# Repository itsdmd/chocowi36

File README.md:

# chocowi36

> A 36-key, low profile, wireless, split keyboard. Derived from [davidphilipbarr/Choc-Spaced-Corne](https://github.com/davidphilipbarr/Choc-Spaced-Corne), with the original design based on [Foostan's Corne](https://github.com/foostan/crkbd).

## Changes

-   The PCB shape, dimensions and mounting holes' position are modified to personal preferences.
-   Battery onboard connector is replaced with through hole pads for better flexibility. Power switch is connected to the positive terminal of the battery instead of ground.
-   The outermost thumb key has been changed to a 1u key, and the splayed angle of the thumb cluster has been increased to 15 degrees.
-   Allow the nice!nano to be mounted with the USB port facing down for both halves for better MCB protection.
-   Support both hotswap and soldered switches. Only Choc v1 switches are supported.

## Case

The case for the keyboard can be found here: [OnShape document](https://cad.onshape.com/documents/46b39ce86a53def7590272f1/w/488db377576b09efc6e15f6f/e/8a81a5fcc0753b2088ec2435)

This case features a 5.5x2.1 DC power jack for connecting to a detachable Li-Ion battery enclosure. The provided enclosure is designed for storing a 21700 battery with a protection PCB attached to it. This enclosure can act as a tenting mechanism, or for locking the two keyboard halves in place when folded for travelling. Most parameters can be _slightly_ adjust without breaking the whole thing. The screw holes are 3.0mm in diameter (for housing M2 heat inserts), and default tolerance is 0.3-0.5mm.

## Firmware

ZMK shield definition of chocowi36 can be obtained [here](https://github.com/itsdmd/zmk-dongle/tree/N!N_v2/config/boards/shields/chocowi36). Please note that the definition files are written for the keyboard to be used with a third nice!nano as the central/dongle.

The provided files should only act as the boilerplate, please adjust the configurations according to your personal needs and preferences. You can create your own repo using the [template](https://github.com/itsdmd/zmk-dongle) and make further modifications.

## Notes

There are two versions of the PCB, one with [straight traces](./pcb/gerber/straight/straight.zip) and one with [curved traces](./pcb/gerber/rounded/rounded.zip). There are no major differences between the two, mostly just aesthetics.

## Disclaimer

This is a **personal project** and not affiliated with the original authors. The gerber file has been checked against JLCPCB's DFM checker and no critical error was found. All files (including firmware) are provided as-is, **without any warranty or support**.

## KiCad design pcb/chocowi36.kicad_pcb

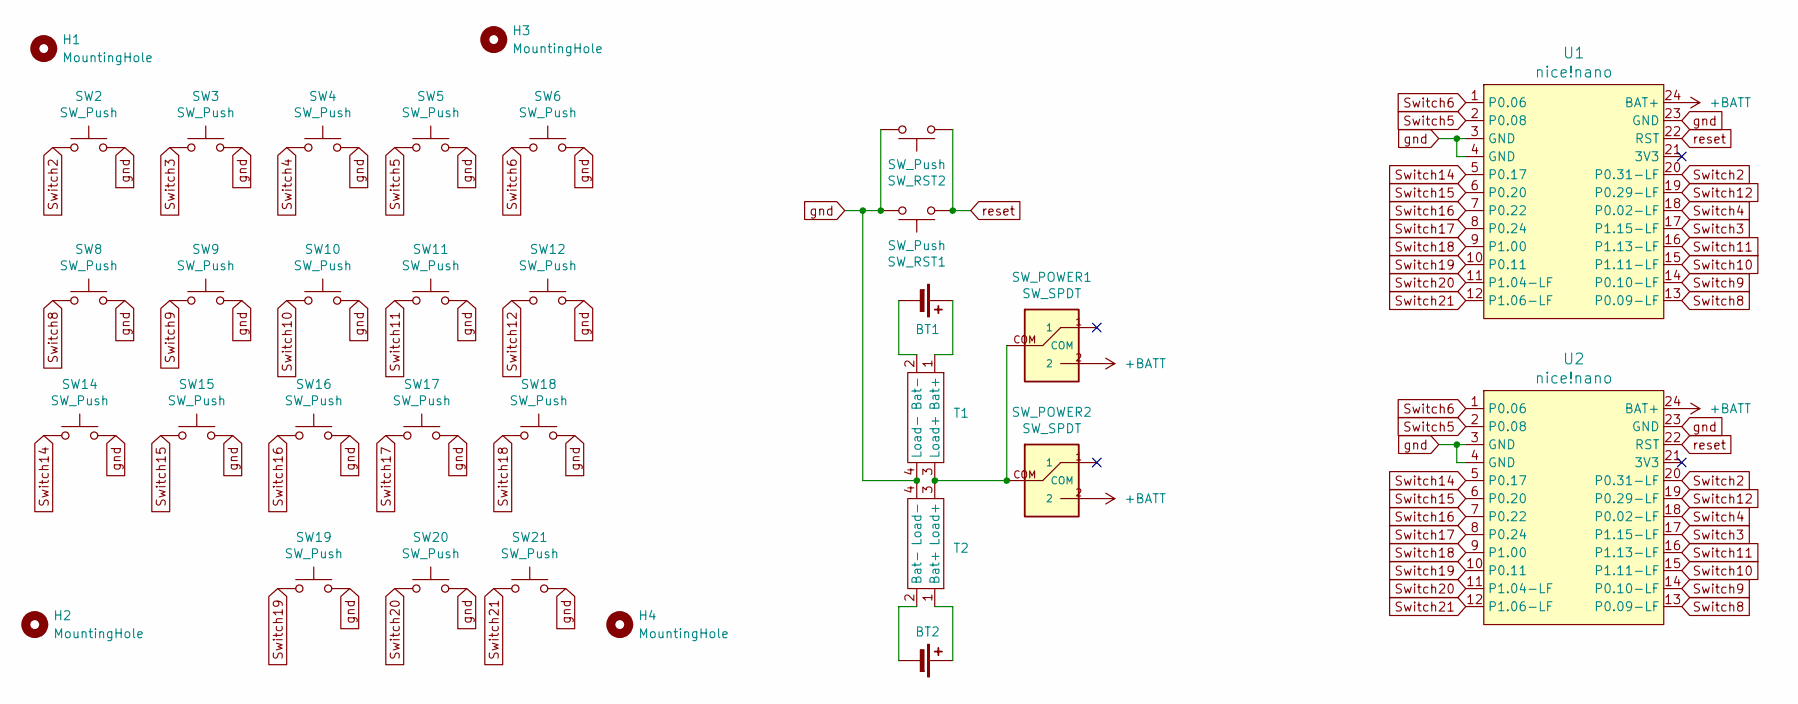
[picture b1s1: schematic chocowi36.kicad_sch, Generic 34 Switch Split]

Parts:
BT1, BT2: B1; Battery_Pads-dual-side
H1, H2, H3, H4: MountingHole; MountingHole_2.2mm_M2
SW2, SW3, SW4, SW5, SW6, SW8, SW9, SW10, SW11, SW12, SW14, SW15, SW16, SW17, SW18, SW19, SW20, SW21: SW_Push; KS_Socket_Choc_optional_reversible
SW_POWER1, SW_POWER2: SW_SPDT; SW-S_MSK-12C02
SW_RST1, SW_RST2: SW_Push; SW-T_SPST_TL3342
T1, T2: Module_TP4056_Mini-SMD_Interface
U1, U2: nice!nano; MCB_nice-nano_flip

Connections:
+BATT: SW_POWER1.2, SW_POWER2.2, U1.24 (BAT+), U2.24 (BAT+)
unnamed: BT1.1 (+), T1.1 (Bat+)
unnamed: BT1.2 (-), T1.2 (Bat-)
unnamed: BT2.1 (+), T2.1 (Bat+)
unnamed: BT2.2 (-), T2.2 (Bat-)
unnamed: SW_POWER1.COM, SW_POWER2.COM, T1.3 (Load+), T2.3 (Load+)
Switch2: SW2.1, U1.20 (P0.31-LF), U2.20 (P0.31-LF)
Switch3: SW3.1, U1.17 (P1.15-LF), U2.17 (P1.15-LF)
Switch4: SW4.1, U1.18 (P0.02-LF), U2.18 (P0.02-LF)
Switch5: SW5.1, U1.2 (P0.08), U2.2 (P0.08)
Switch6: SW6.1, U1.1 (P0.06), U2.1 (P0.06)
Switch8: SW8.1, U1.13 (P0.09-LF), U2.13 (P0.09-LF)
Switch9: SW9.1, U1.14 (P0.10-LF), U2.14 (P0.10-LF)
Switch10: SW10.1, U1.15 (P1.11-LF), U2.15 (P1.11-LF)
Switch11: SW11.1, U1.16 (P1.13-LF), U2.16 (P1.13-LF)
Switch12: SW12.1, U1.19 (P0.29-LF), U2.19 (P0.29-LF)
Switch14: SW14.1, U1.5 (P0.17), U2.5 (P0.17)
Switch15: SW15.1, U1.6 (P0.20), U2.6 (P0.20)
Switch16: SW16.1, U1.7 (P0.22), U2.7 (P0.22)
Switch17: SW17.1, U1.8 (P0.24), U2.8 (P0.24)
Switch18: SW18.1, U1.9 (P1.00), U2.9 (P1.00)
Switch19: SW19.1, U1.10 (P0.11), U2.10 (P0.11)
Switch20: SW20.1, U1.11 (P1.04-LF), U2.11 (P1.04-LF)
Switch21: SW21.1, U1.12 (P1.06-LF), U2.12 (P1.06-LF)
gnd: SW2.2, SW3.2, SW4.2, SW5.2, SW6.2, SW8.2, SW9.2, SW10.2, SW11.2, SW12.2, SW14.2, SW15.2, SW16.2, SW17.2, SW18.2, SW19.2, SW20.2, SW21.2, SW_RST1.1, SW_RST2.1, T1.4 (Load-), T2.4 (Load-), U1.3 (GND), U1.4 (GND), U1.23 (GND), U2.3 (GND), U2.4 (GND), U2.23 (GND)
reset: SW_RST1.2, SW_RST2.2, U1.22 (RST), U2.22 (RST)

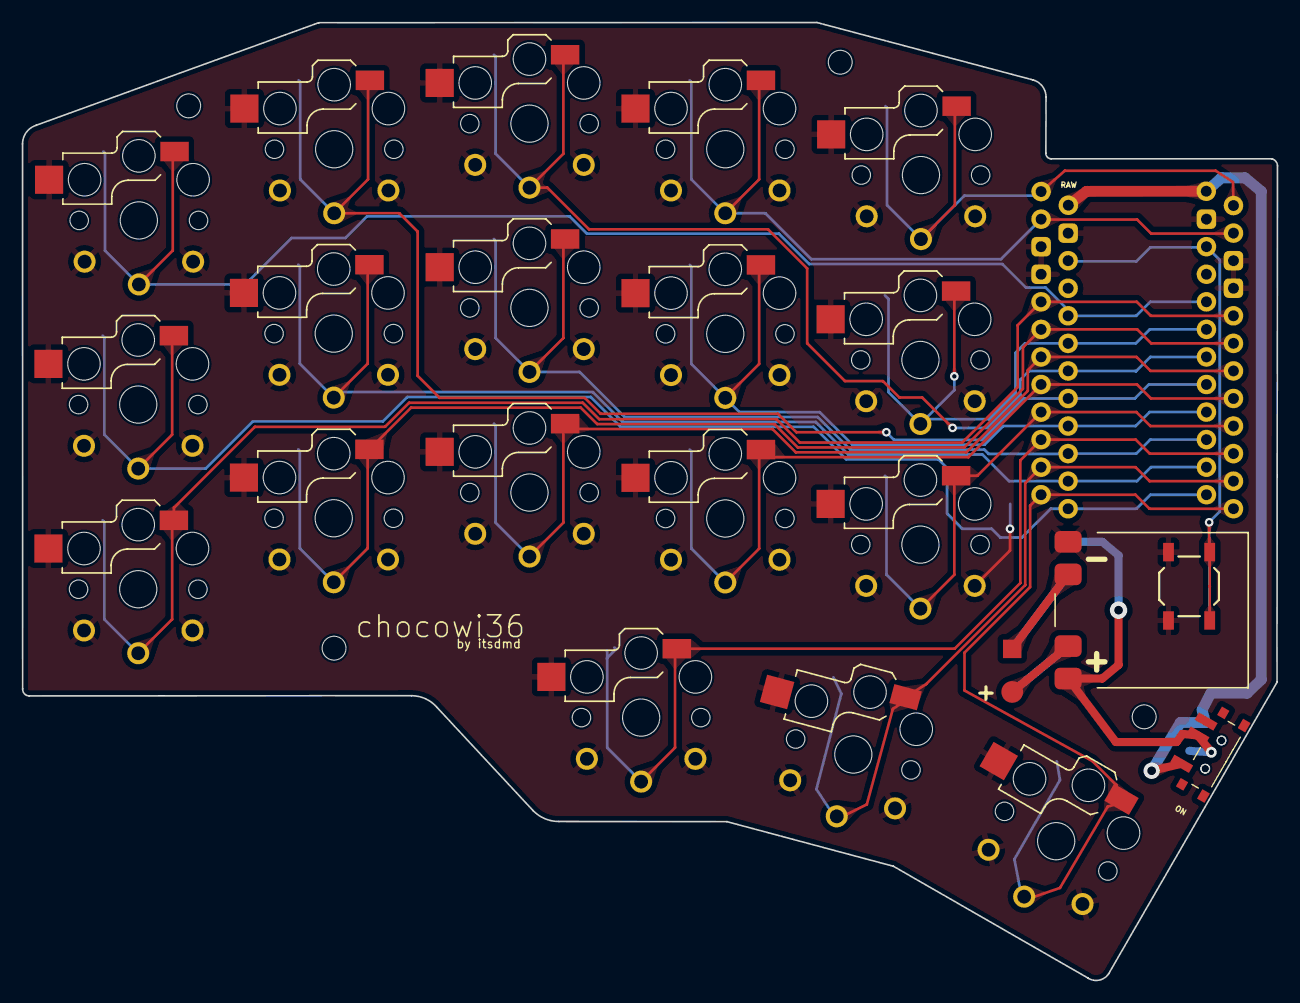
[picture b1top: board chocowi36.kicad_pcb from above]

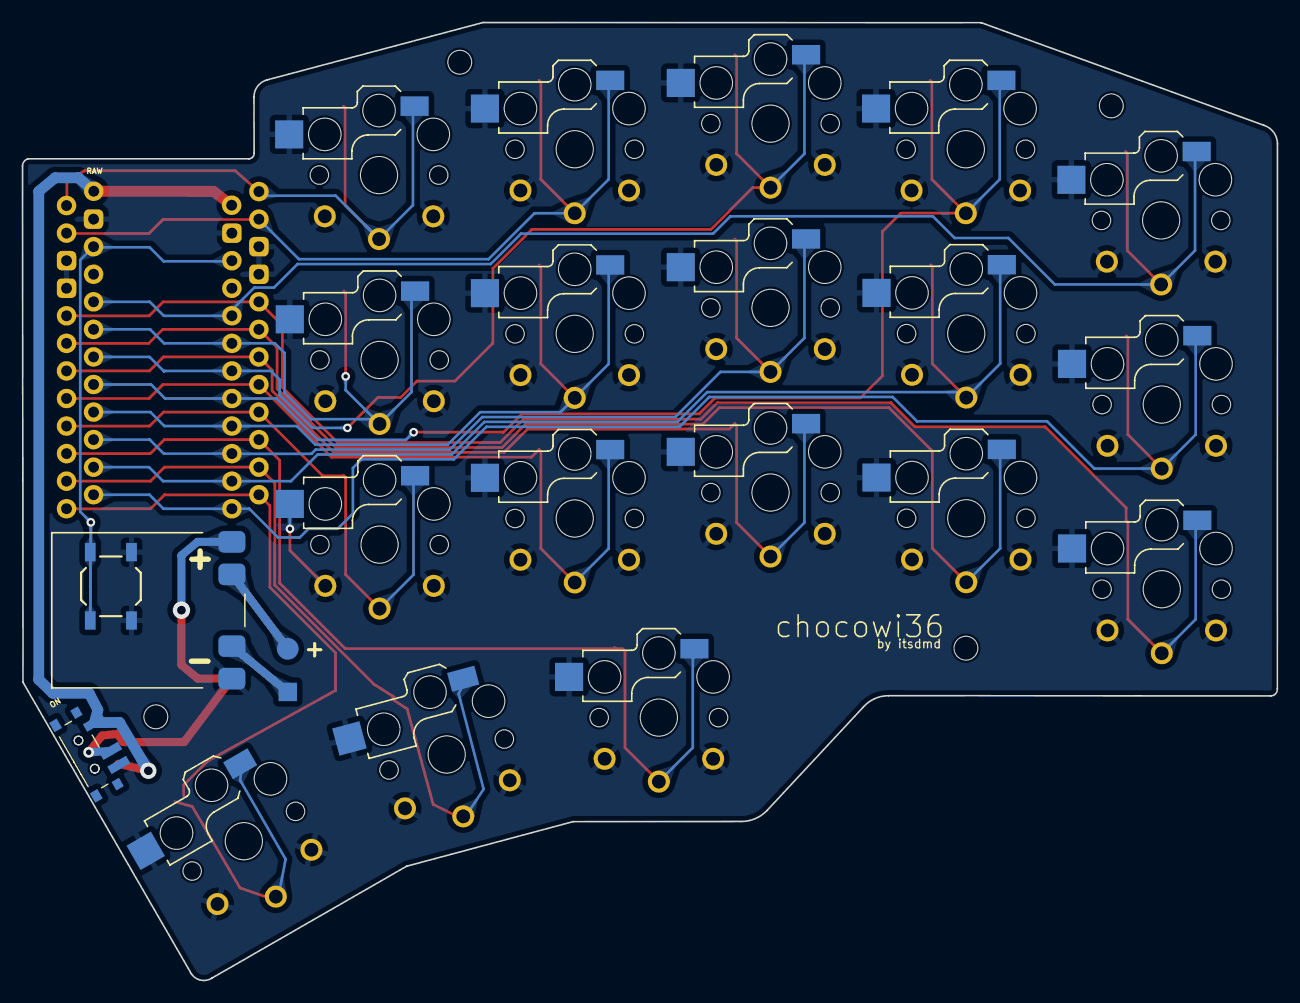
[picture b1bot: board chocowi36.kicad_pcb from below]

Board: 2 copper layers, 115.7 x 88.3 mm, 32 parts (5 on the bottom side), 26 nets.

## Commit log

2024-09-02 initial modifications
2024-09-02 rename to chocowi36
2024-09-02 small changes + update doc
2024-09-02 small update
2024-09-02 adjust thumb cluster
2024-09-03 fix thumb cluster
2024-09-06 add case step & stl files
2024-09-07 update case design
2024-09-07 update doc
2024-09-09 add case image
2024-10-29 update routing to support placing tactile switches on both sides
2024-11-17 add tp4056 charging module, update edge.cut
    change power button position
2024-11-17 update gerber
2024-11-18 minor improvements
2024-11-18 update case files
2024-11-18 slight changes
